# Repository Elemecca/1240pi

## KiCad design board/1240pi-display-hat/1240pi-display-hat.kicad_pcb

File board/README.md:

## Copying

Copyright 2022 Sam Hanes

The documentation in this directory describes Open Hardware and is
licensed under the CERN-OHL-S version 2 or any later version.

You may redistribute and modify this source and make products using it
under the terms of the [CERN-OHL-S v2+](https://ohwr.org/cern_ohl_s_v2.txt).

This source is distributed WITHOUT ANY EXPRESS OR IMPLIED WARRANTY,
INCLUDING OF MERCHANTABILITY, SATISFACTORY QUALITY AND FITNESS FOR
A PARTICULAR PURPOSE. Please see the CERN-OHL-S v2+ for applicable
conditions.

Source location: https://github.com/Elemecca/1240pi

As per CERN-OHL-S v2 section 4, should You produce hardware based
on this source, You must where practicable maintain the Source Location
visible on the external case of the products you make using this source.

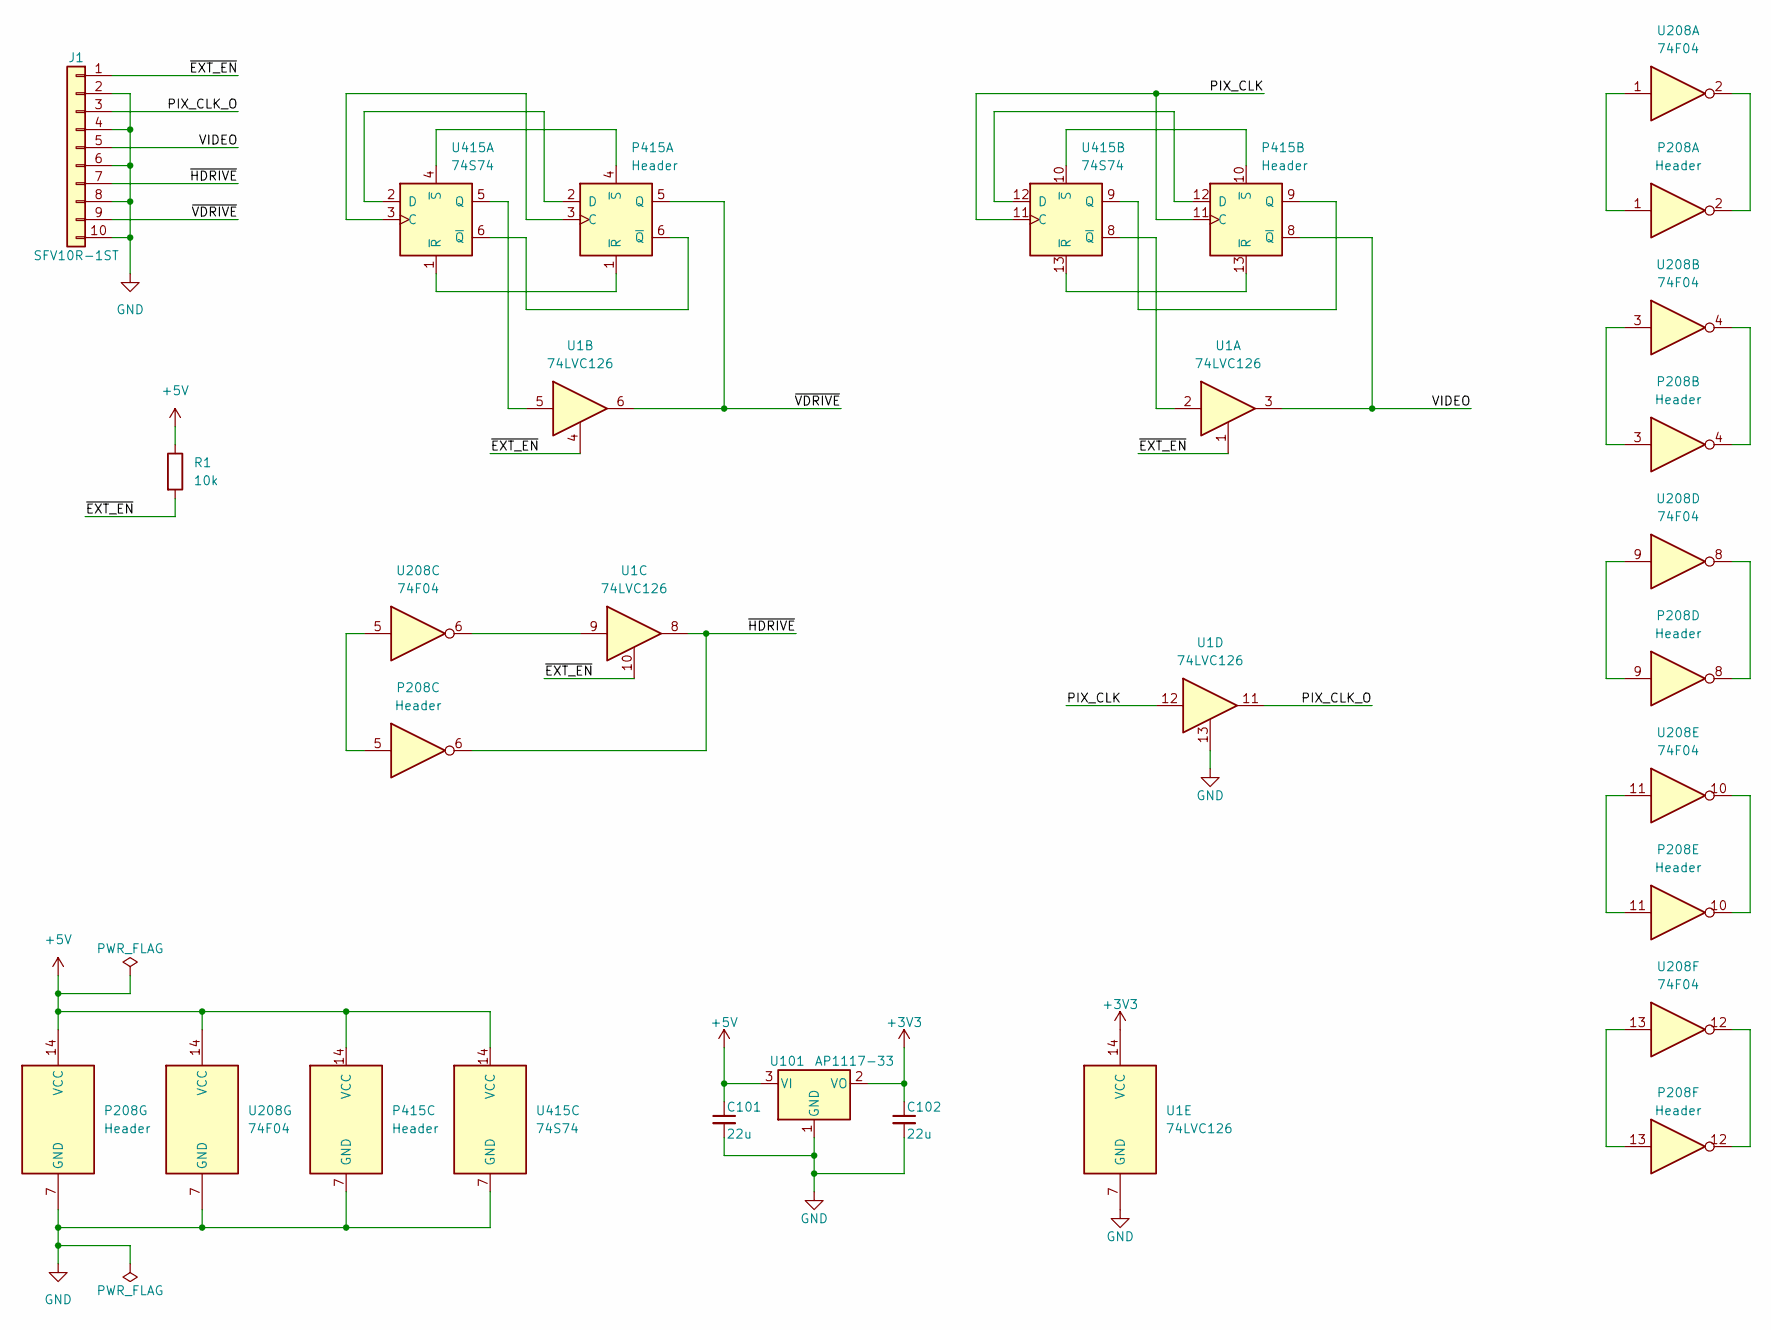
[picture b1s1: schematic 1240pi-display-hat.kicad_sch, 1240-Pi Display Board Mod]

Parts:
C101, C102: 22u; C_0805_2012Metric
J1: SFV10R-1ST; Amphenol_SFV10R-1ST
P208, P415: Header; DIP-14_W7.62mm
R1: 10k; R_Axial_DIN0207_L6.3mm_D2.5mm_P10.16mm_Horizontal
U1: 74LVC126; SO-14_3.9x8.65mm_P1.27mm
U101: AP1117-33; SOT-223-3_TabPin2
U208: 74F04; DIP-14_W7.62mm
U415: 74S74; DIP-14_W7.62mm

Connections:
+3V3: C102.1, U1.14 (VCC), U101.2 (VO)
+5V: C101.1, P208.14 (VCC), P415.14 (VCC), R1.1, U101.3 (VI), U208.14 (VCC), U415.14 (VCC)
/PIX_CLK: P415.11 (C), U1.12, U415.11 (C)
/PIX_CLK_O: J1.3, U1.11
/VIDEO: J1.5, P415.8 (~Q), U1.3
/~EXT_EN: J1.1, R1.2, U1.1, U1.4, U1.10
/~HDRIVE: J1.7, P208.6, U1.8
/~VDRIVE: J1.9, P415.5 (Q), U1.6
GND: C101.2, C102.2, J1.2, J1.4, J1.6, J1.8, J1.10, P208.7 (GND), P415.7 (GND), U1.7 (GND), U1.13, U101.1 (GND), U208.7 (GND), U415.7 (GND)
unnamed: P208.1, U208.1
unnamed: P208.2, U208.2
unnamed: P208.3, U208.3
unnamed: P208.4, U208.4
unnamed: P208.5, U208.5
unnamed: P208.8, U208.8
unnamed: P208.9, U208.9
unnamed: P208.10, U208.10
unnamed: P208.11, U208.11
unnamed: P208.12, U208.12
unnamed: P208.13, U208.13
unnamed: P415.1 (~R), U415.1 (~R)
unnamed: P415.2 (D), U415.2 (D)
unnamed: P415.3 (C), U415.3 (C)
unnamed: P415.4 (~S), U415.4 (~S)
unnamed: P415.6 (~Q), U415.6 (~Q)
unnamed: P415.9 (Q), U415.9 (Q)
unnamed: P415.10 (~S), U415.10 (~S)
unnamed: P415.12 (D), U415.12 (D)
unnamed: P415.13 (~R), U415.13 (~R)
unnamed: U1.2, U415.8 (~Q)
unnamed: U1.5, U415.5 (Q)
unnamed: U1.9, U208.6

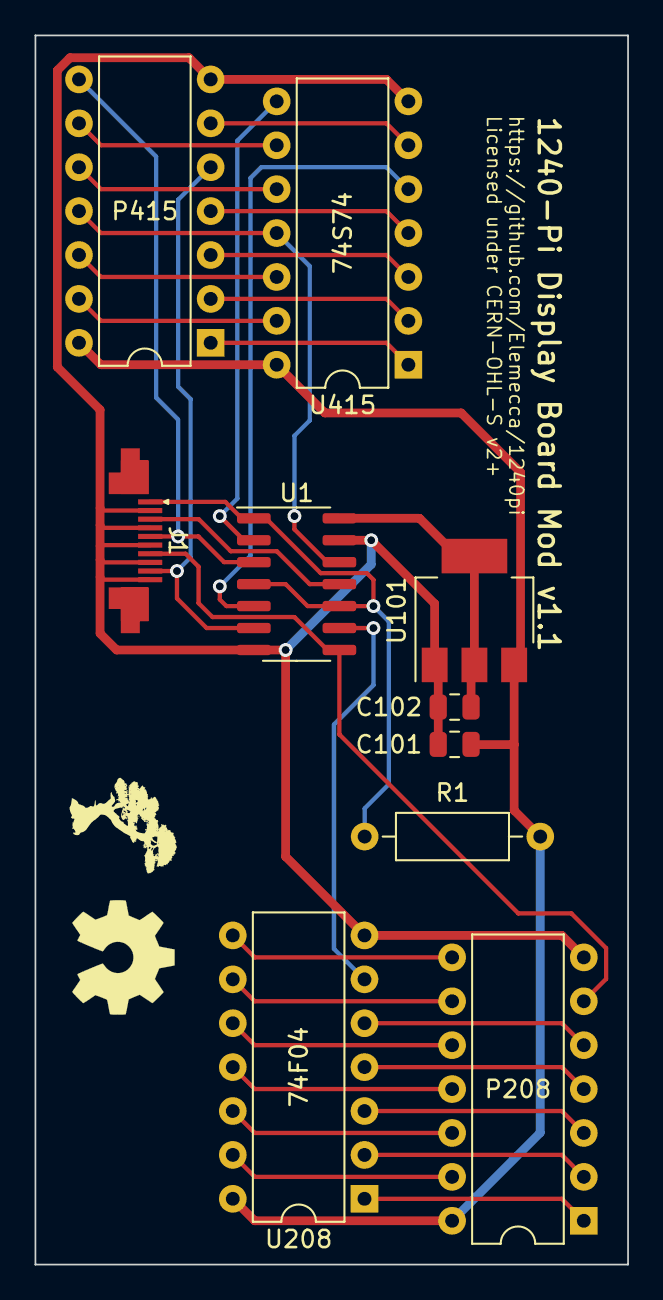
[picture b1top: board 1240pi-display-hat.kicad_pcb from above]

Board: 2 copper layers, 34.3 x 71.1 mm, 10 parts (0 on the bottom side), 32 nets.

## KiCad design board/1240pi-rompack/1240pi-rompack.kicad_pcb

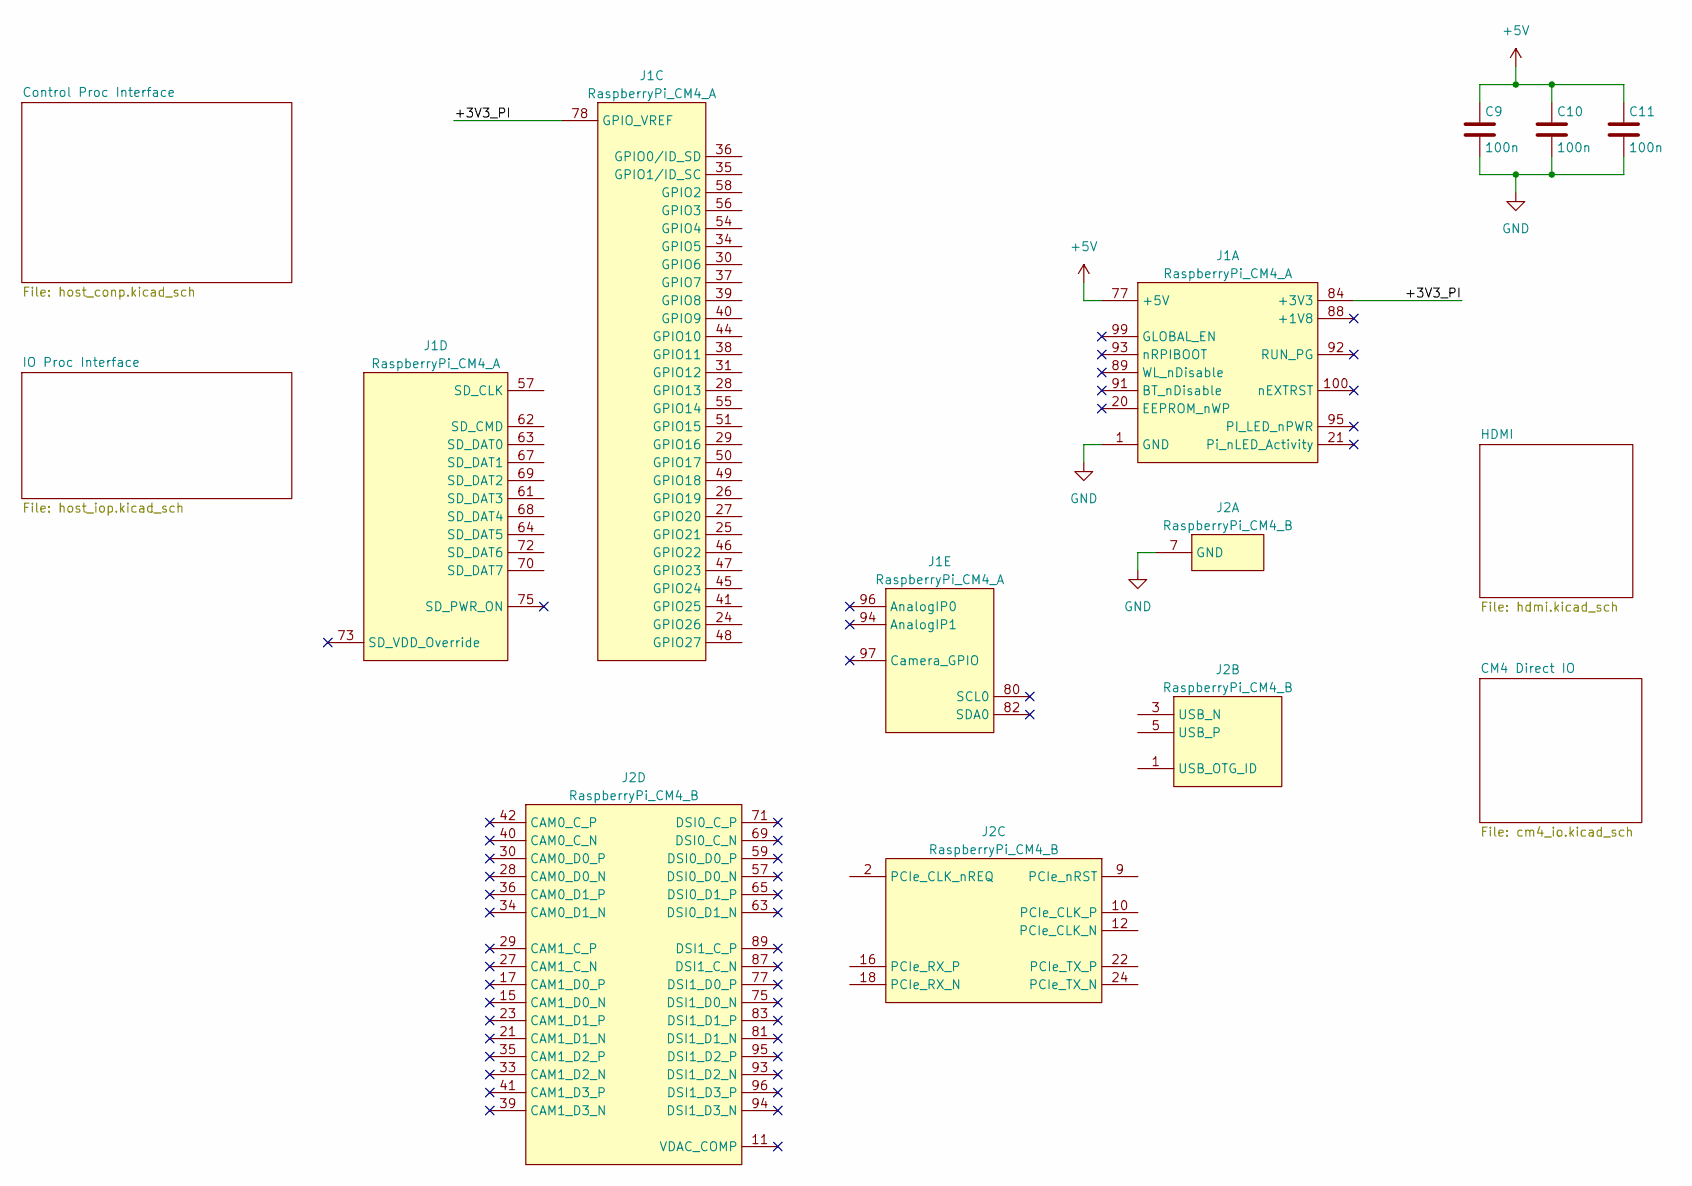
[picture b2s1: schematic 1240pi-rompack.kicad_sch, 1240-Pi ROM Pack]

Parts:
C9, C10, C11: 100n; C_0603_1608Metric
J1: RaspberryPi_CM4_A; Hirose_DF40C-100DS-0.4V
J2: RaspberryPi_CM4_B; Hirose_DF40C-100DS-0.4V

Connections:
+5V: C9.1, C10.1, C11.1, J1.77 (+5V), J1.79 (+5V), J1.81 (+5V), J1.83 (+5V), J1.85 (+5V), J1.87 (+5V); also elsewhere on the board
/+3V3_PI: J1.78 (GPIO_VREF), J1.84 (+3V3), J1.86 (+3V3)
GND: C9.2, C10.2, C11.2, J1.1 (GND), J1.2 (GND), J1.7 (GND), J1.8 (GND), J1.13 (GND), J1.14 (GND), J1.22 (GND), J1.23 (GND), J1.32 (GND), J1.33 (GND), J1.42 (GND), J1.43 (GND), J1.52 (GND), J1.53 (GND), J1.59 (GND), J1.60 (GND), J1.65 (GND), J1.66 (GND), J1.71 (GND), J1.74 (GND), J1.98 (GND), J2.7 (GND), J2.8 (GND), J2.13 (GND), J2.14 (GND), J2.19 (GND), J2.20 (GND), J2.25 (GND), J2.26 (GND), J2.31 (GND), J2.32 (GND), J2.37 (GND), J2.38 (GND), J2.44 (GND), J2.50 (GND), J2.55 (GND), J2.56 (GND), J2.61 (GND), J2.62 (GND), J2.67 (GND), J2.68 (GND), J2.73 (GND), J2.74 (GND), J2.79 (GND), J2.80 (GND), J2.85 (GND), J2.86 (GND), J2.91 (GND), J2.92 (GND), J2.97 (GND), J2.98 (GND); also elsewhere on the board

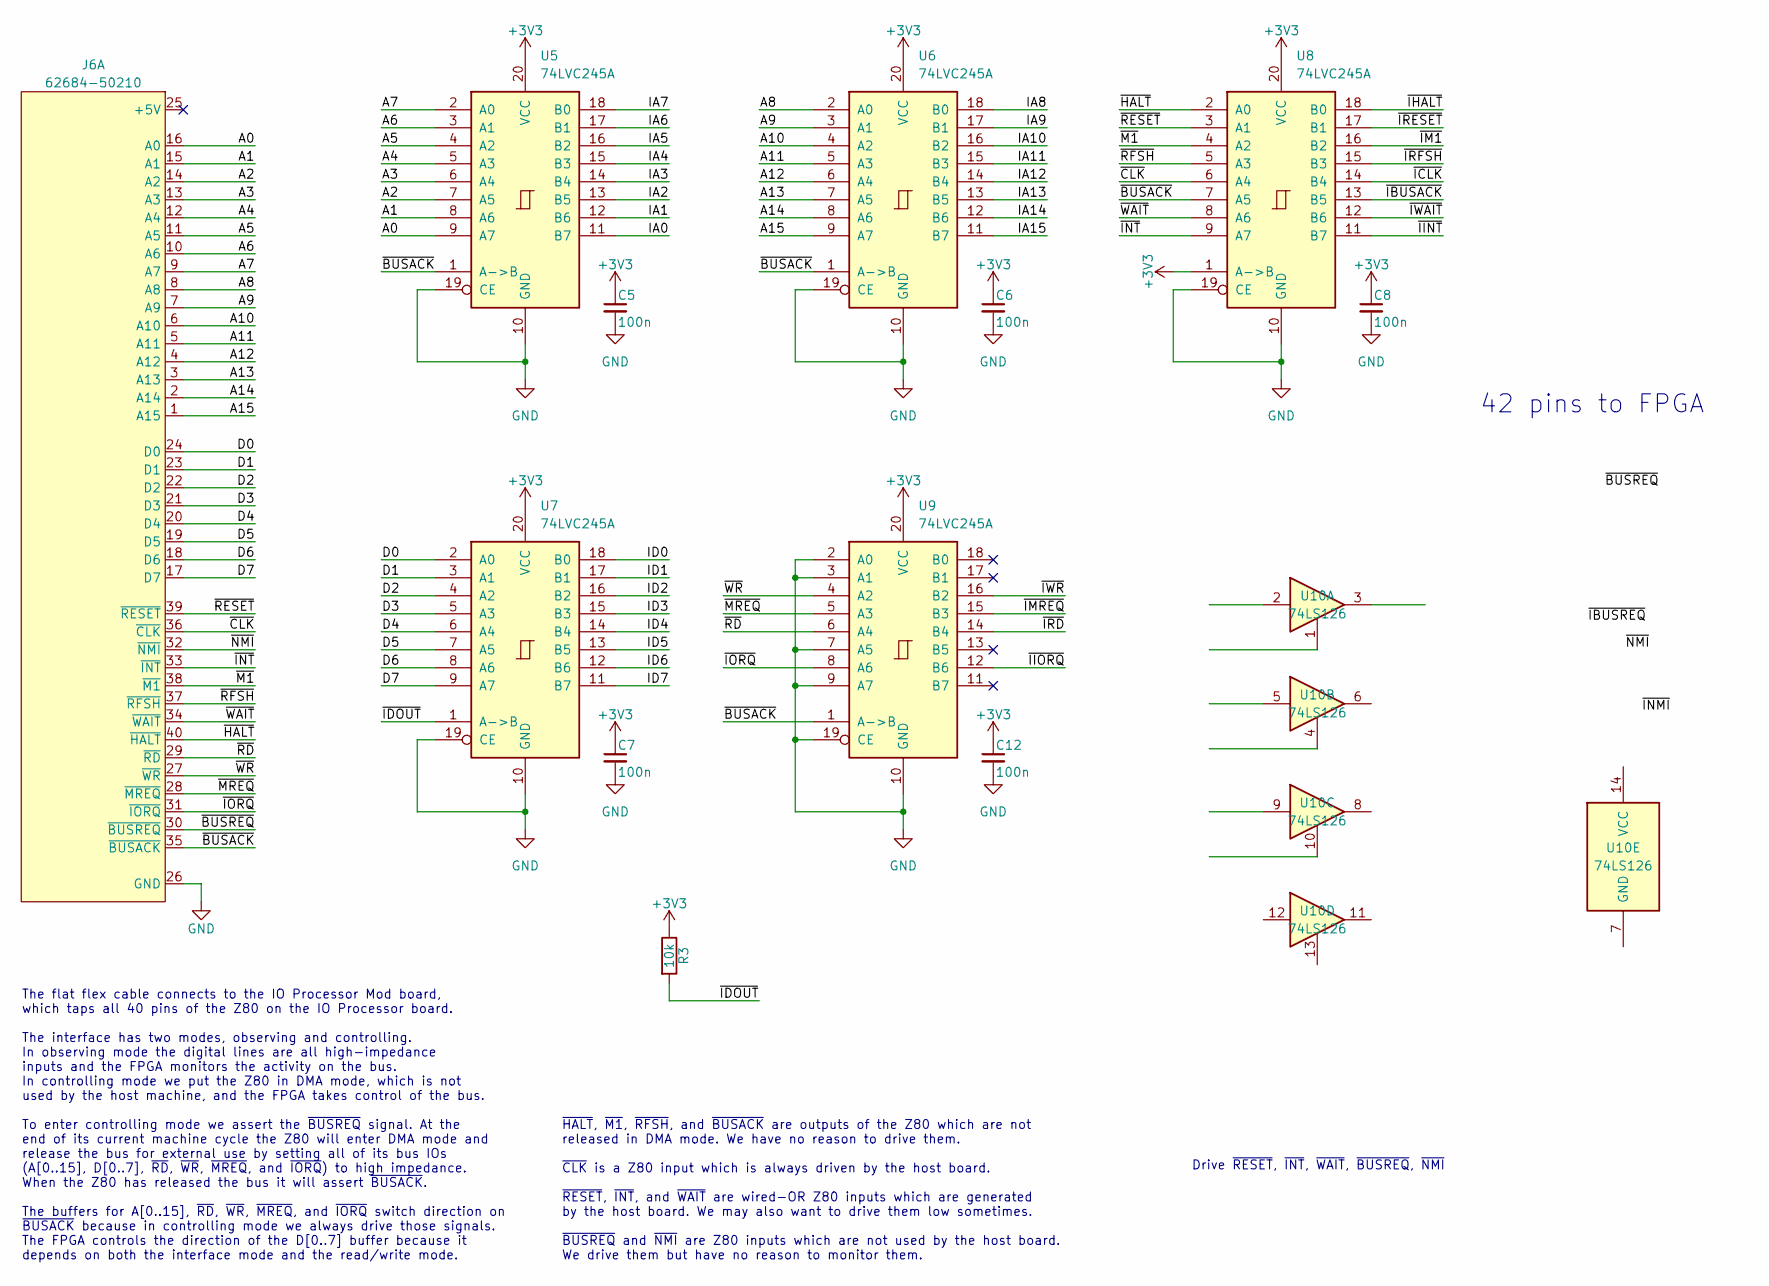
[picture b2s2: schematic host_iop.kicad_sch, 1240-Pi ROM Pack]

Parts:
C5, C6, C7, C8, C12: 100n; C_0402_1005Metric
J6: 62684-50210; Amphenol_62684-50210
R3: 10k; R_0402_1005Metric
U5, U6, U7, U8, U9: 74LVC245A; Nexperia_SOT764-1
U10: 74LS126

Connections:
+3V3: C5.1, C6.1, C7.1, C8.1, C12.1, R3.1, U5.20 (VCC), U6.20 (VCC), U7.20 (VCC), U8.1 (A->B), U8.20 (VCC), U9.20 (VCC); also elsewhere on the board
/IO Proc Interface/A0: J6.16 (A0), U5.9 (A7)
/IO Proc Interface/A1: J6.15 (A1), U5.8 (A6)
/IO Proc Interface/A2: J6.14 (A2), U5.7 (A5)
/IO Proc Interface/A3: J6.13 (A3), U5.6 (A4)
/IO Proc Interface/A4: J6.12 (A4), U5.5 (A3)
/IO Proc Interface/A5: J6.11 (A5), U5.4 (A2)
/IO Proc Interface/A6: J6.10 (A6), U5.3 (A1)
/IO Proc Interface/A7: J6.9 (A7), U5.2 (A0)
/IO Proc Interface/A8: J6.8 (A8), U6.2 (A0)
/IO Proc Interface/A9: J6.7 (A9), U6.3 (A1)
/IO Proc Interface/A10: J6.6 (A10), U6.4 (A2)
/IO Proc Interface/A11: J6.5 (A11), U6.5 (A3)
/IO Proc Interface/A12: J6.4 (A12), U6.6 (A4)
/IO Proc Interface/A13: J6.3 (A13), U6.7 (A5)
/IO Proc Interface/A14: J6.2 (A14), U6.8 (A6)
/IO Proc Interface/A15: J6.1 (A15), U6.9 (A7)
/IO Proc Interface/D0: J6.24 (D0), U7.2 (A0)
/IO Proc Interface/D1: J6.23 (D1), U7.3 (A1)
/IO Proc Interface/D2: J6.22 (D2), U7.4 (A2)
/IO Proc Interface/D3: J6.21 (D3), U7.5 (A3)
/IO Proc Interface/D4: J6.20 (D4), U7.6 (A4)
/IO Proc Interface/D5: J6.19 (D5), U7.7 (A5)
/IO Proc Interface/D6: J6.18 (D6), U7.8 (A6)
/IO Proc Interface/D7: J6.17 (D7), U7.9 (A7)
/IO Proc Interface/IA0: U5.11 (B7)
/IO Proc Interface/IA1: U5.12 (B6)
/IO Proc Interface/IA2: U5.13 (B5)
/IO Proc Interface/IA3: U5.14 (B4)
/IO Proc Interface/IA4: U5.15 (B3)
/IO Proc Interface/IA5: U5.16 (B2)
/IO Proc Interface/IA6: U5.17 (B1)
/IO Proc Interface/IA7: U5.18 (B0)
/IO Proc Interface/IA8: U6.18 (B0)
/IO Proc Interface/IA9: U6.17 (B1)
/IO Proc Interface/IA10: U6.16 (B2)
/IO Proc Interface/IA11: U6.15 (B3)
/IO Proc Interface/IA12: U6.14 (B4)
/IO Proc Interface/IA13: U6.13 (B5)
/IO Proc Interface/IA14: U6.12 (B6)
/IO Proc Interface/IA15: U6.11 (B7)
/IO Proc Interface/ID0: U7.18 (B0)
/IO Proc Interface/ID1: U7.17 (B1)
/IO Proc Interface/ID2: U7.16 (B2)
/IO Proc Interface/ID3: U7.15 (B3)
/IO Proc Interface/ID4: U7.14 (B4)
/IO Proc Interface/ID5: U7.13 (B5)
/IO Proc Interface/ID6: U7.12 (B6)
/IO Proc Interface/ID7: U7.11 (B7)
/IO Proc Interface/~BUSACK: J6.35 (~BUSACK), U5.1 (A->B), U6.1 (A->B), U8.7 (A5), U9.1 (A->B)
/IO Proc Interface/~BUSREQ: J6.30 (~BUSREQ)
/IO Proc Interface/~CLK: J6.36 (~CLK), U8.6 (A4)
/IO Proc Interface/~HALT: J6.40 (~HALT), U8.2 (A0)
/IO Proc Interface/~IBUSACK: U8.13 (B5)
/IO Proc Interface/~ICLK: U8.14 (B4)
/IO Proc Interface/~IDOUT: R3.2, U7.1 (A->B)
/IO Proc Interface/~IHALT: U8.18 (B0)
/IO Proc Interface/~IINT: U8.11 (B7)
/IO Proc Interface/~IIORQ: U9.12 (B6)
/IO Proc Interface/~IM1: U8.16 (B2)
/IO Proc Interface/~IMREQ: U9.15 (B3)
/IO Proc Interface/~INT: J6.33 (~INT), U8.9 (A7)
/IO Proc Interface/~IORQ: J6.31 (~IORQ), U9.8 (A6)
/IO Proc Interface/~IRD: U9.14 (B4)
/IO Proc Interface/~IRESET: U8.17 (B1)
/IO Proc Interface/~IRFSH: U8.15 (B3)
/IO Proc Interface/~IWAIT: U8.12 (B6)
/IO Proc Interface/~IWR: U9.16 (B2)
/IO Proc Interface/~M1: J6.38 (~M1), U8.4 (A2)
/IO Proc Interface/~MREQ: J6.28 (~MREQ), U9.5 (A3)
/IO Proc Interface/~NMI: J6.32 (~NMI)
/IO Proc Interface/~RD: J6.29 (~RD), U9.6 (A4)
/IO Proc Interface/~RESET: J6.39 (~RESET), U8.3 (A1)
/IO Proc Interface/~RFSH: J6.37 (~RFSH), U8.5 (A3)
/IO Proc Interface/~WAIT: J6.34 (~WAIT), U8.8 (A6)
/IO Proc Interface/~WR: J6.27 (~WR), U9.4 (A2)
GND: C5.2, C6.2, C7.2, C8.2, C12.2, J6.26 (GND), U5.10 (GND), U5.19 (CE), U6.10 (GND), U6.19 (CE), U7.10 (GND), U7.19 (CE), U8.10 (GND), U8.19 (CE), U9.2 (A0), U9.3 (A1), U9.7 (A5), U9.9 (A7), U9.10 (GND), U9.19 (CE); also elsewhere on the board

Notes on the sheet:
Drive ~{RESET}, ~{INT}, ~{WAIT}, ~{BUSREQ}, ~{NMI}
The flat flex cable connects to the IO Processor Mod board, which taps all 40 pins of the Z80 on the IO Processor board. The interface has two modes, observing and controlling. In observing mode the digital lines are all high-impedance inputs and the FPGA monitors the activity on the bus. In contro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
42 pins to FPGA
~{HALT}, ~{M1}, ~{RFSH}, and ~{BUSACK} are outputs of the Z80 which are not released in DMA mode. We have no reason to drive them. ~{CLK} is a Z80 input which is always driven by the host board. ~{RESET}, ~{INT}, and ~{WAIT} are wired-OR Z80 inputs which are generated by the host board. We may also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

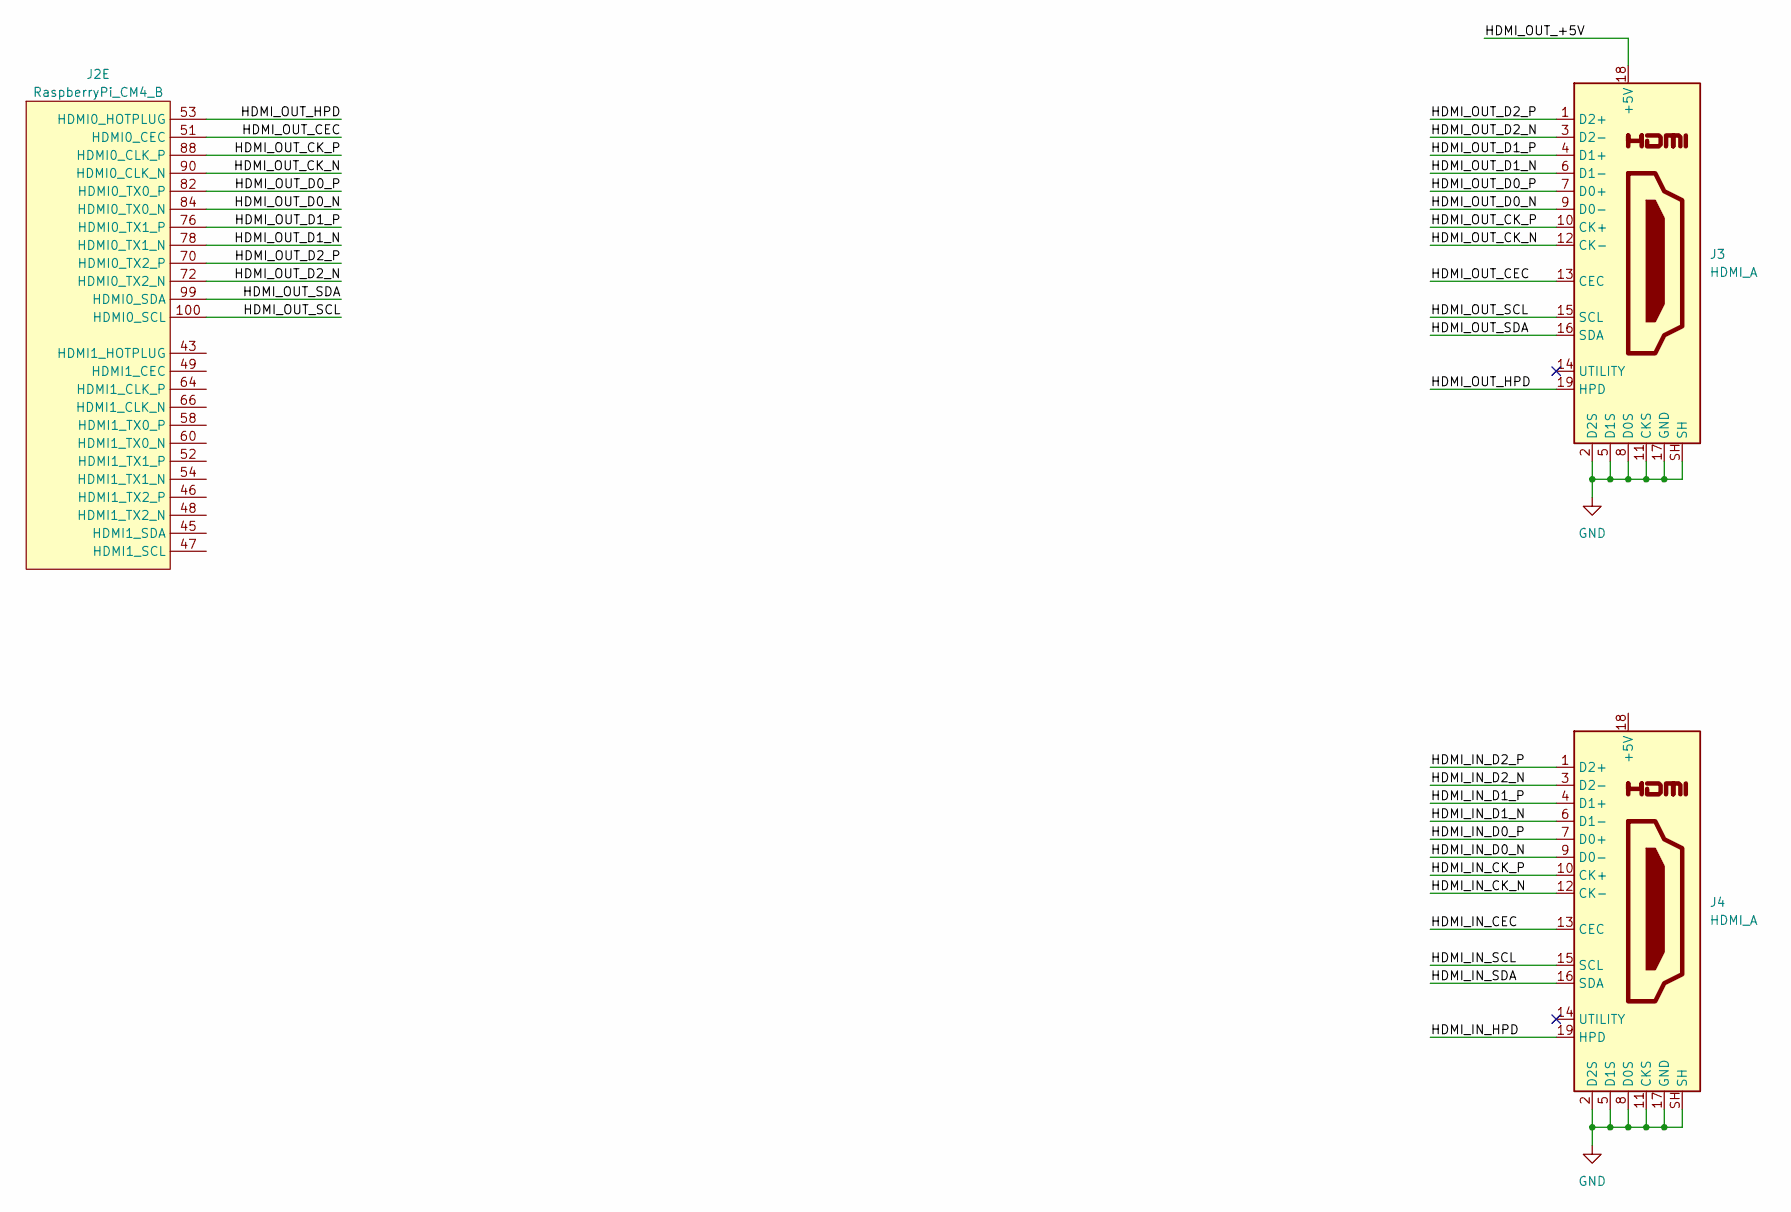
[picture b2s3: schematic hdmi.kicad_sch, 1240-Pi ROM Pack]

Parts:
J2: RaspberryPi_CM4_B; Hirose_DF40C-100DS-0.4V
J3, J4: HDMI_A; CNC_2000-1-2-41-00-BK

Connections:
/HDMI/HDMI_IN_CEC: J4.13 (CEC)
/HDMI/HDMI_IN_CK_N: J4.12 (CK-)
/HDMI/HDMI_IN_CK_P: J4.10 (CK+)
/HDMI/HDMI_IN_D0_N: J4.9 (D0-)
/HDMI/HDMI_IN_D0_P: J4.7 (D0+)
/HDMI/HDMI_IN_D1_N: J4.6 (D1-)
/HDMI/HDMI_IN_D1_P: J4.4 (D1+)
/HDMI/HDMI_IN_D2_N: J4.3 (D2-)
/HDMI/HDMI_IN_D2_P: J4.1 (D2+)
/HDMI/HDMI_IN_HPD: J4.19 (HPD)
/HDMI/HDMI_IN_SCL: J4.15 (SCL)
/HDMI/HDMI_IN_SDA: J4.16 (SDA)
/HDMI/HDMI_OUT_+5V: J3.18 (+5V)
/HDMI/HDMI_OUT_CEC: J2.51 (HDMI0_CEC), J3.13 (CEC)
/HDMI/HDMI_OUT_CK_N: J2.90 (HDMI0_CLK_N), J3.12 (CK-)
/HDMI/HDMI_OUT_CK_P: J2.88 (HDMI0_CLK_P), J3.10 (CK+)
/HDMI/HDMI_OUT_D0_N: J2.84 (HDMI0_TX0_N), J3.9 (D0-)
/HDMI/HDMI_OUT_D0_P: J2.82 (HDMI0_TX0_P), J3.7 (D0+)
/HDMI/HDMI_OUT_D1_N: J2.78 (HDMI0_TX1_N), J3.6 (D1-)
/HDMI/HDMI_OUT_D1_P: J2.76 (HDMI0_TX1_P), J3.4 (D1+)
/HDMI/HDMI_OUT_D2_N: J2.72 (HDMI0_TX2_N), J3.3 (D2-)
/HDMI/HDMI_OUT_D2_P: J2.70 (HDMI0_TX2_P), J3.1 (D2+)
/HDMI/HDMI_OUT_HPD: J2.53 (HDMI0_HOTPLUG), J3.19 (HPD)
/HDMI/HDMI_OUT_SCL: J2.100 (HDMI0_SCL), J3.15 (SCL)
/HDMI/HDMI_OUT_SDA: J2.99 (HDMI0_SDA), J3.16 (SDA)
GND: J3.2 (D2S), J3.5 (D1S), J3.8 (D0S), J3.11 (CKS), J3.17 (GND), J3.SH, J4.2 (D2S), J4.5 (D1S), J4.8 (D0S), J4.11 (CKS), J4.17 (GND), J4.SH; also elsewhere on the board

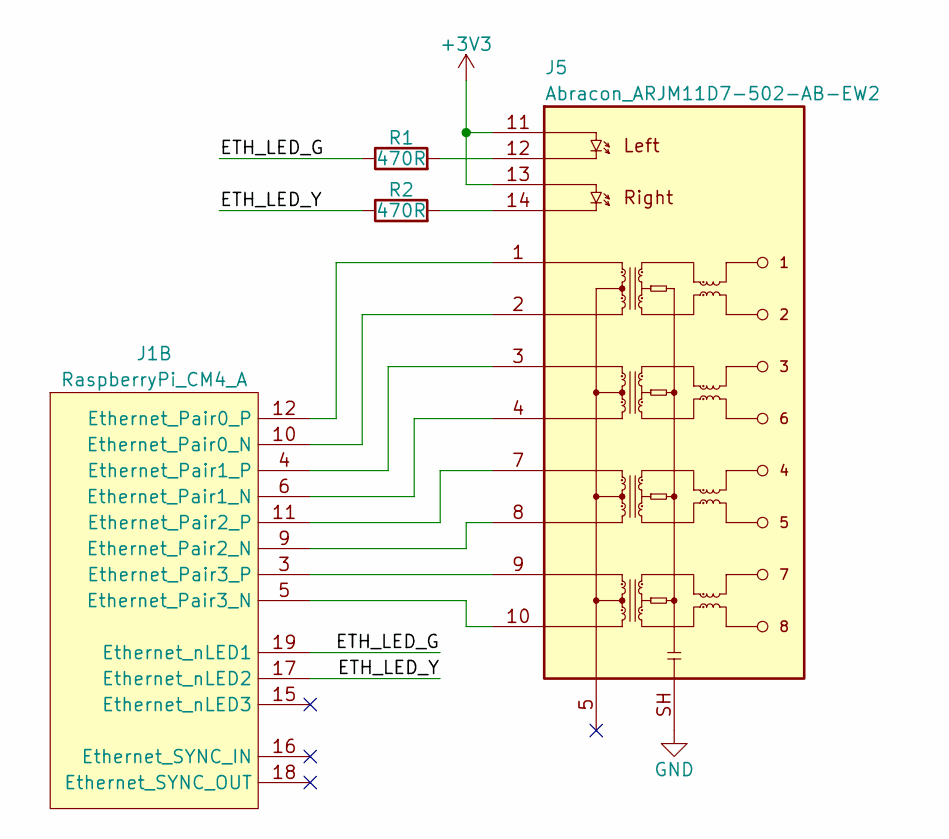
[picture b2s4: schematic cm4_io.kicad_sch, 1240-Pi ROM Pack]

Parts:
J1: RaspberryPi_CM4_A; Hirose_DF40C-100DS-0.4V
J5: Abracon_ARJM11D7-502-AB-EW2
R1, R2: 470R; R_0603_1608Metric

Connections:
+3V3: J5.11 (LED1+), J5.13 (LED2+); also elsewhere on the board
/CM4 Direct IO/ETH_LED_G: J1.19 (Ethernet_nLED1), R1.1
/CM4 Direct IO/ETH_LED_Y: J1.17 (Ethernet_nLED2), R2.1
GND: J5.SH; also elsewhere on the board
unnamed: J1.3 (Ethernet_Pair3_P), J5.9 (TD4+)
unnamed: J1.4 (Ethernet_Pair1_P), J5.3 (TD2+)
unnamed: J1.5 (Ethernet_Pair3_N), J5.10 (TD4-)
unnamed: J1.6 (Ethernet_Pair1_N), J5.4 (TD2-)
unnamed: J1.9 (Ethernet_Pair2_N), J5.8 (TD3-)
unnamed: J1.10 (Ethernet_Pair0_N), J5.2 (TD2-)
unnamed: J1.11 (Ethernet_Pair2_P), J5.7 (TD3+)
unnamed: J1.12 (Ethernet_Pair0_P), J5.1 (TD2+)
unnamed: J5.12 (LED1-), R1.2
unnamed: J5.14 (LED2-), R2.2

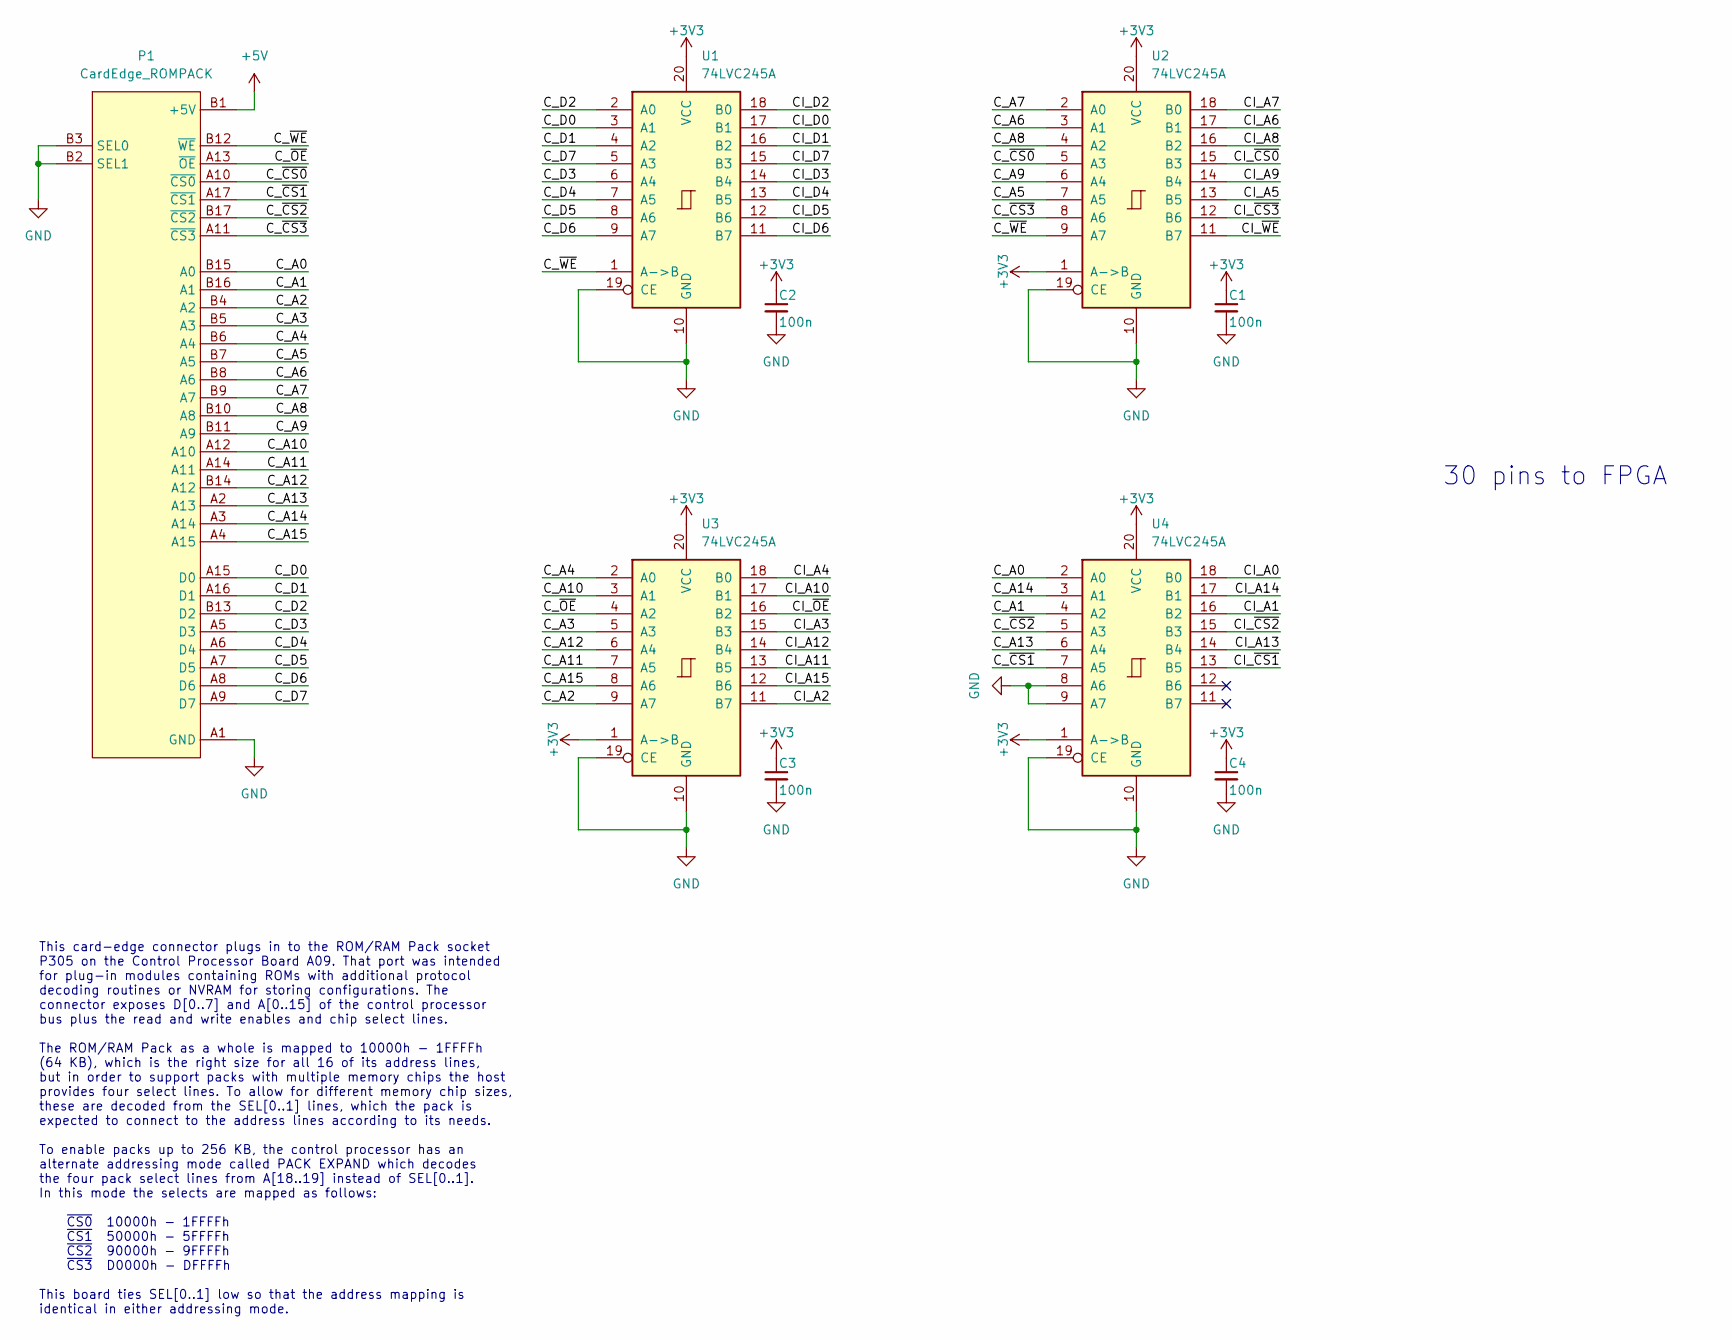
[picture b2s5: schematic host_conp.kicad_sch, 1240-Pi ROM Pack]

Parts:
C1, C2, C3, C4: 100n; C_0402_1005Metric
P1: CardEdge_ROMPACK; CardEdge_18x2
U1, U2, U3, U4: 74LVC245A; Nexperia_SOT764-1

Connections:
+3V3: C1.1, C2.1, C3.1, C4.1, U1.20 (VCC), U2.1 (A->B), U2.20 (VCC), U3.1 (A->B), U3.20 (VCC), U4.1 (A->B), U4.20 (VCC); also elsewhere on the board
+5V: P1.B1 (+5V), P1.B18 (+5V); also elsewhere on the board
/Control Proc Interface/CI_A0: U4.18 (B0)
/Control Proc Interface/CI_A1: U4.16 (B2)
/Control Proc Interface/CI_A2: U3.11 (B7)
/Control Proc Interface/CI_A3: U3.15 (B3)
/Control Proc Interface/CI_A4: U3.18 (B0)
/Control Proc Interface/CI_A5: U2.13 (B5)
/Control Proc Interface/CI_A6: U2.17 (B1)
/Control Proc Interface/CI_A7: U2.18 (B0)
/Control Proc Interface/CI_A8: U2.16 (B2)
/Control Proc Interface/CI_A9: U2.14 (B4)
/Control Proc Interface/CI_A10: U3.17 (B1)
/Control Proc Interface/CI_A11: U3.13 (B5)
/Control Proc Interface/CI_A12: U3.14 (B4)
/Control Proc Interface/CI_A13: U4.14 (B4)
/Control Proc Interface/CI_A14: U4.17 (B1)
/Control Proc Interface/CI_A15: U3.12 (B6)
/Control Proc Interface/CI_D0: U1.17 (B1)
/Control Proc Interface/CI_D1: U1.16 (B2)
/Control Proc Interface/CI_D2: U1.18 (B0)
/Control Proc Interface/CI_D3: U1.14 (B4)
/Control Proc Interface/CI_D4: U1.13 (B5)
/Control Proc Interface/CI_D5: U1.12 (B6)
/Control Proc Interface/CI_D6: U1.11 (B7)
/Control Proc Interface/CI_D7: U1.15 (B3)
/Control Proc Interface/CI_~CS0: U2.15 (B3)
/Control Proc Interface/CI_~CS1: U4.13 (B5)
/Control Proc Interface/CI_~CS2: U4.15 (B3)
/Control Proc Interface/CI_~CS3: U2.12 (B6)
/Control Proc Interface/CI_~OE: U3.16 (B2)
/Control Proc Interface/CI_~WE: U2.11 (B7)
/Control Proc Interface/C_A0: P1.B15 (A0), U4.2 (A0)
/Control Proc Interface/C_A1: P1.B16 (A1), U4.4 (A2)
/Control Proc Interface/C_A2: P1.B4 (A2), U3.9 (A7)
/Control Proc Interface/C_A3: P1.B5 (A3), U3.5 (A3)
/Control Proc Interface/C_A4: P1.B6 (A4), U3.2 (A0)
/Control Proc Interface/C_A5: P1.B7 (A5), U2.7 (A5)
/Control Proc Interface/C_A6: P1.B8 (A6), U2.3 (A1)
/Control Proc Interface/C_A7: P1.B9 (A7), U2.2 (A0)
/Control Proc Interface/C_A8: P1.B10 (A8), U2.4 (A2)
/Control Proc Interface/C_A9: P1.B11 (A9), U2.6 (A4)
/Control Proc Interface/C_A10: P1.A12 (A10), U3.3 (A1)
/Control Proc Interface/C_A11: P1.A14 (A11), U3.7 (A5)
/Control Proc Interface/C_A12: P1.B14 (A12), U3.6 (A4)
/Control Proc Interface/C_A13: P1.A2 (A13), U4.6 (A4)
/Control Proc Interface/C_A14: P1.A3 (A14), U4.3 (A1)
/Control Proc Interface/C_A15: P1.A4 (A15), U3.8 (A6)
/Control Proc Interface/C_D0: P1.A15 (D0), U1.3 (A1)
/Control Proc Interface/C_D1: P1.A16 (D1), U1.4 (A2)
/Control Proc Interface/C_D2: P1.B13 (D2), U1.2 (A0)
/Control Proc Interface/C_D3: P1.A5 (D3), U1.6 (A4)
/Control Proc Interface/C_D4: P1.A6 (D4), U1.7 (A5)
/Control Proc Interface/C_D5: P1.A7 (D5), U1.8 (A6)
/Control Proc Interface/C_D6: P1.A8 (D6), U1.9 (A7)
/Control Proc Interface/C_D7: P1.A9 (D7), U1.5 (A3)
/Control Proc Interface/C_~CS0: P1.A10 (~CS0), U2.5 (A3)
/Control Proc Interface/C_~CS1: P1.A17 (~CS1), U4.7 (A5)
/Control Proc Interface/C_~CS2: P1.B17 (~CS2), U4.5 (A3)
/Control Proc Interface/C_~CS3: P1.A11 (~CS3), U2.8 (A6)
/Control Proc Interface/C_~OE: P1.A13 (~OE), U3.4 (A2)
/Control Proc Interface/C_~WE: P1.B12 (~WE), U1.1 (A->B), U2.9 (A7)
GND: C1.2, C2.2, C3.2, C4.2, P1.A1 (GND), P1.A18 (GND), P1.B2 (SEL1), P1.B3 (SEL0), U1.10 (GND), U1.19 (CE), U2.10 (GND), U2.19 (CE), U3.10 (GND), U3.19 (CE), U4.8 (A6), U4.9 (A7), U4.10 (GND), U4.19 (CE); also elsewhere on the board

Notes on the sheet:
This card-edge connector plugs in to the ROM/RAM Pack socket P305 on the Control Processor Board A09. That port was intended for plug-in modules containing ROMs with additional protocol decoding routines or NVRAM for storing configurations. The connector exposes D[0..7] and A[0..15] of the control 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
30 pins to FPGA

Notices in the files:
board/1240pi-display-hat/1240pi-display-hat.kicad_pcb:
© 2022 Sam Hanes, licensed under CERN-OHL-S v2+
board/1240pi-hats/1240pi-hats.kicad_pcb:
Licensed under CERN-OHL-P v2
